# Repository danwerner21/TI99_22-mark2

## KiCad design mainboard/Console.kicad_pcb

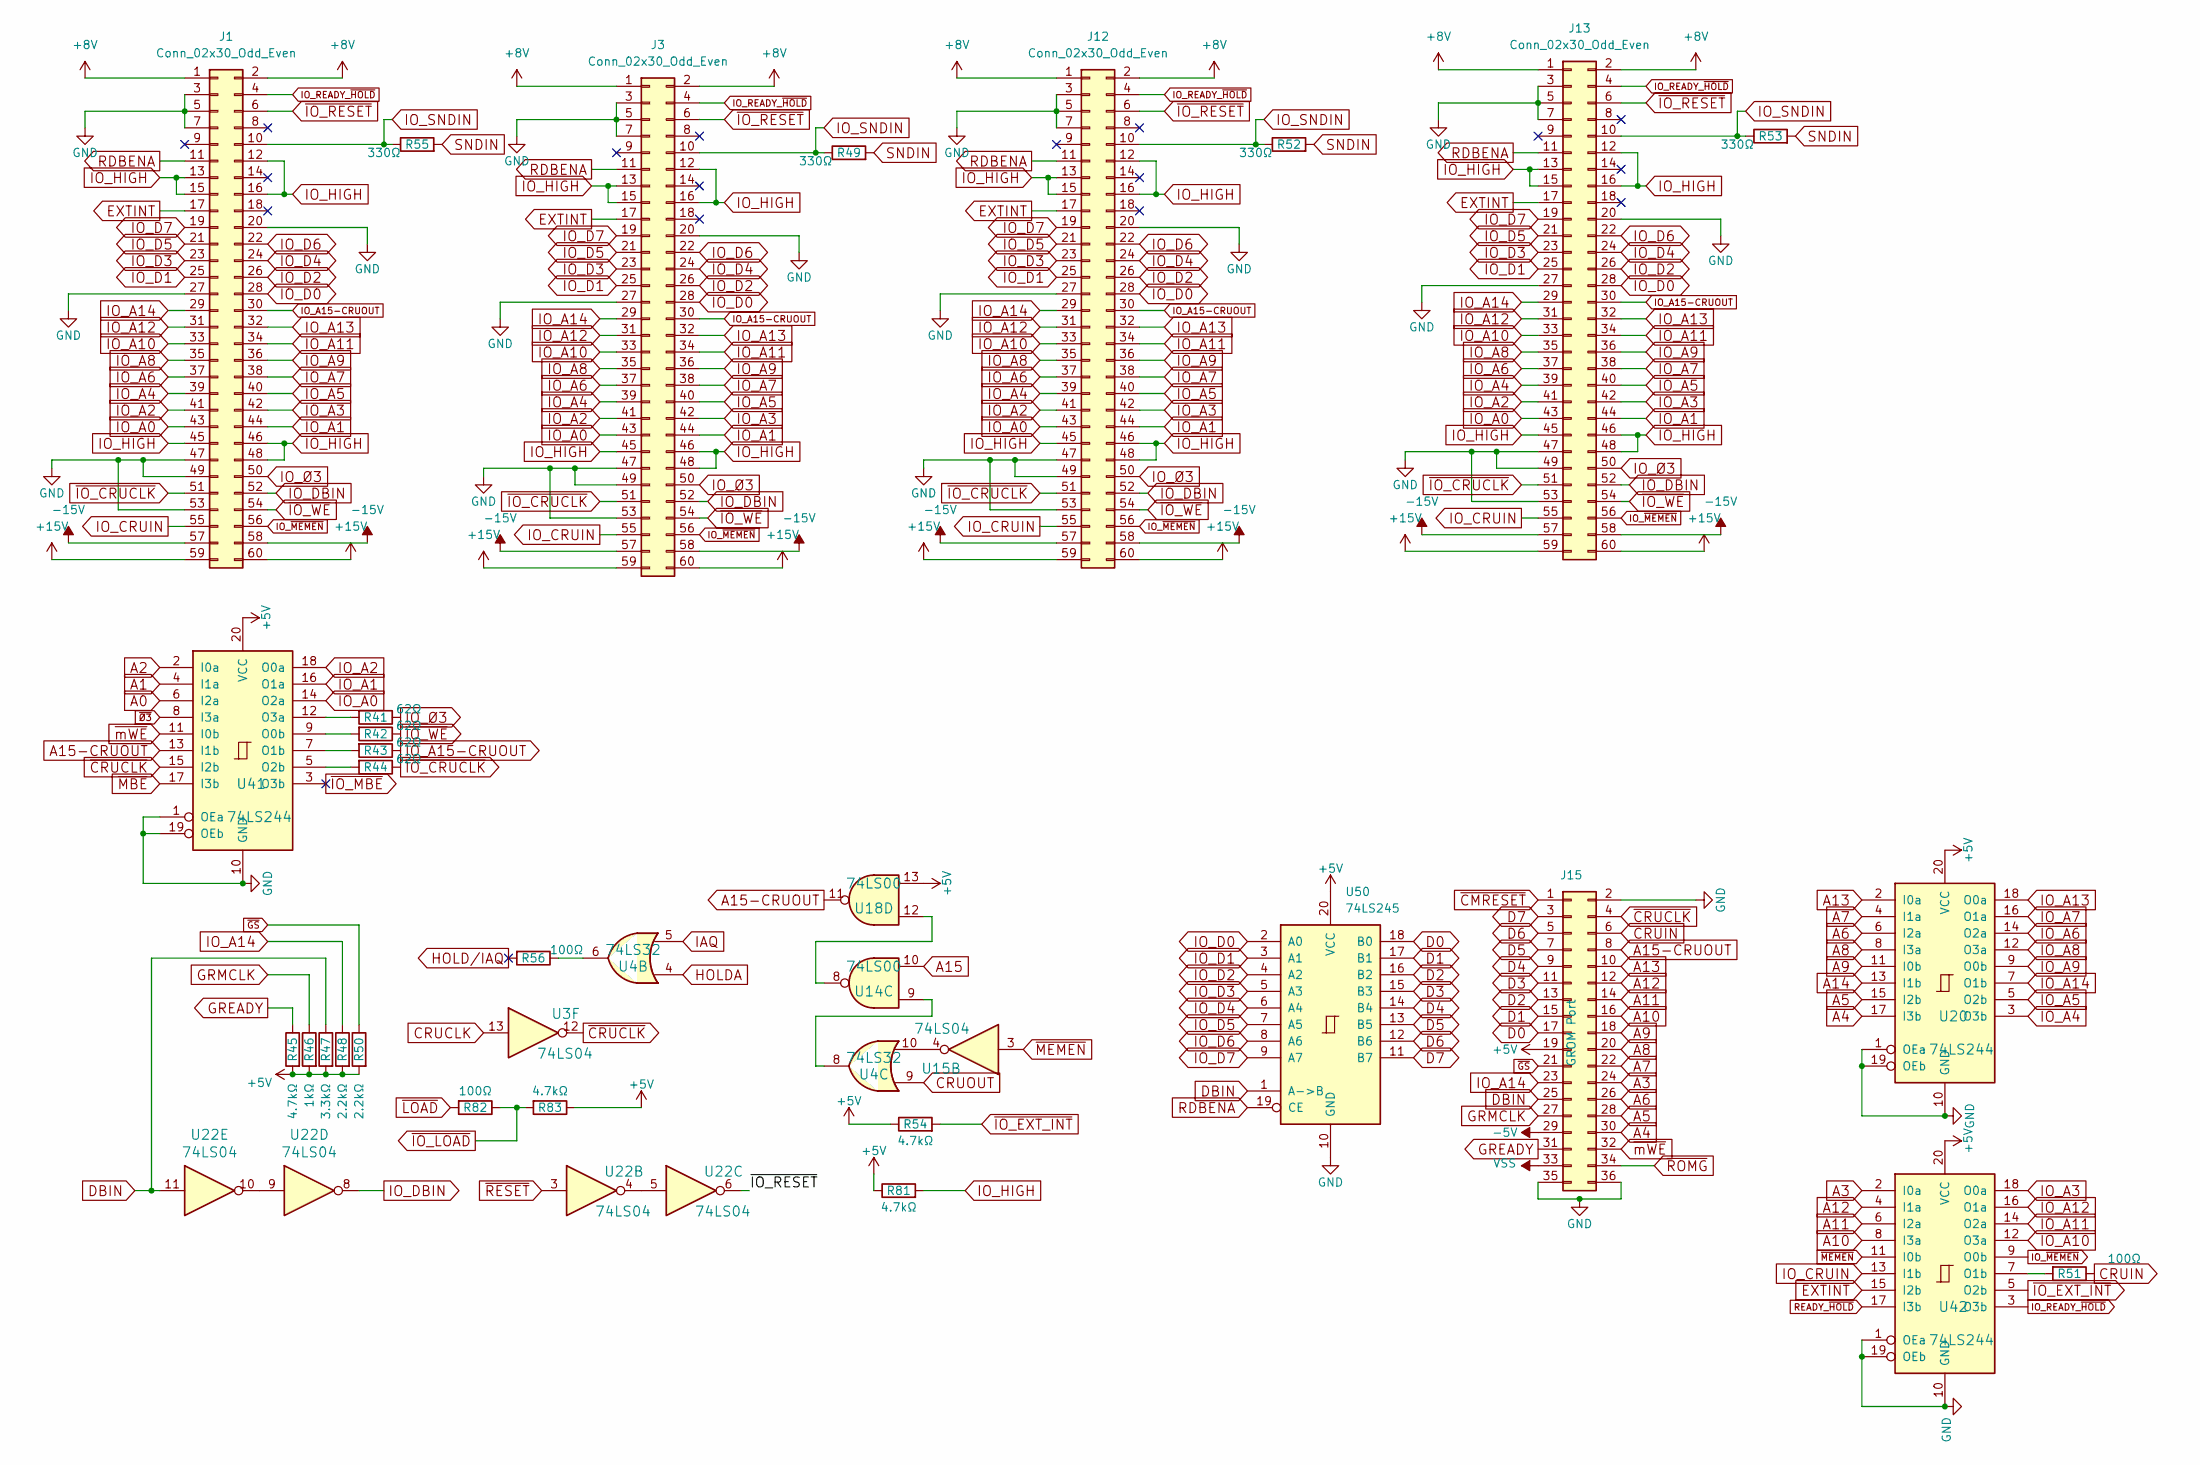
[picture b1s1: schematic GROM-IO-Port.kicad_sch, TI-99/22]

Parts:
J1, J3, J12, J13: Conn_02x30_Odd_Even; STD_DDW_CARDEDGE60
J15: GROM Port; STD_DDW_PINHEAD_V_2x18
R41, R42, R43, R44: 62Ω; STD_DDW_RESISTOR
R45, R54, R81, R83: 4.7kΩ; STD_DDW_RESISTOR
R46: 1kΩ; STD_DDW_RESISTOR
R47: 3.3kΩ; STD_DDW_RESISTOR
R48, R50: 2.2kΩ; STD_DDW_RESISTOR
R49, R52, R53, R55: 330Ω; STD_DDW_RESISTOR
R51, R56, R82: 100Ω; STD_DDW_RESISTOR
U3, U15, U22: 74LS04; STD_DDW_DIP14
U4: 74LS32; STD_DDW_DIP14
U14, U18: 74LS00; STD_DDW_DIP14
U20, U41, U42: 74LS244; STD_DDW_DIP20
U50: 74LS245; STD_DDW_DIP20

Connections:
+5V: J15.19, R45.2, R46.2, R47.2, R48.2, R50.2, R54.1, R81.1, R83.1, U18.13, U20.20 (VCC), U41.20 (VCC), U42.20 (VCC), U50.20 (VCC); also elsewhere on the board
+8V: J1.1, J1.2, J3.1, J3.2, J12.1, J12.2, J13.1, J13.2; also elsewhere on the board
+15V: J1.59, J1.60, J3.59, J3.60, J12.59, J12.60, J13.59, J13.60; also elsewhere on the board
-5V: J15.29; also elsewhere on the board
-15V: J1.57, J1.58, J3.57, J3.58, J12.57, J12.58, J13.57, J13.58; also elsewhere on the board
A0: U41.6 (I2a); also elsewhere on the board
A1: U41.4 (I1a); also elsewhere on the board
A2: U41.2 (I0a); also elsewhere on the board
A3: J15.24, U42.2 (I0a); also elsewhere on the board
A4: J15.30, U20.17 (I3b); also elsewhere on the board
A5: J15.28, U20.15 (I2b); also elsewhere on the board
A6: J15.26, U20.6 (I2a); also elsewhere on the board
A7: J15.22, U20.4 (I1a); also elsewhere on the board
A8: J15.20, U20.8 (I3a); also elsewhere on the board
A9: J15.18, U20.11 (I0b); also elsewhere on the board
A10: J15.16, U42.8 (I3a); also elsewhere on the board
A11: J15.14, U42.6 (I2a); also elsewhere on the board
A12: J15.12, U42.4 (I1a); also elsewhere on the board
A13: J15.10, U20.2 (I0a); also elsewhere on the board
A14: U20.13 (I1b); also elsewhere on the board
A15: U14.10; also elsewhere on the board
A15-CRUOUT: J15.8, U18.11, U41.13 (I1b); also elsewhere on the board
CRUCLK: U3.13; also elsewhere on the board
CRUIN: J15.6, R51.1; also elsewhere on the board
CRUOUT: U4.9; also elsewhere on the board
D0: J15.17, U50.18 (B0); also elsewhere on the board
D1: J15.15, U50.17 (B1); also elsewhere on the board
D2: J15.13, U50.16 (B2); also elsewhere on the board
D3: J15.11, U50.15 (B3); also elsewhere on the board
D4: J15.9, U50.14 (B4); also elsewhere on the board
D5: J15.7, U50.13 (B5); also elsewhere on the board
D6: J15.5, U50.12 (B6); also elsewhere on the board
D7: J15.3, U50.11 (B7); also elsewhere on the board
DBIN: J15.25, R47.1, U22.11, U50.1 (A->B); also elsewhere on the board
EXTINT: J1.17, J3.17, J12.17, J13.17, U42.15 (I2b); also elsewhere on the board
GND: J1.3, J1.5, J1.7, J1.20, J1.27, J1.47, J1.49, J1.53, J3.3, J3.5, J3.7, J3.20, J3.27, J3.47, J3.49, J3.53, J12.3, J12.5, J12.7, J12.20, J12.27, J12.47, J12.49, J12.53, J13.3, J13.5, J13.7, J13.20, J13.27, J13.47, J13.49, J13.53, J15.2, J15.35, J15.36, U20.1 (OEa), U20.10 (GND), U20.19 (OEb), U41.1 (OEa), U41.10 (GND), U41.19 (OEb), U42.1 (OEa), U42.10 (GND), U42.19 (OEb), U50.10 (GND); also elsewhere on the board
GREADY: J15.31, R45.1; also elsewhere on the board
GRMCLK: J15.27, R46.1; also elsewhere on the board
HOLDA: U4.4; also elsewhere on the board
HOLD/IAQ: R56.2
IAQ: U4.5; also elsewhere on the board
IO_A0: J1.43, J3.43, J12.43, J13.43, U41.14 (O2a)
IO_A1: J1.44, J3.44, J12.44, J13.44, U41.16 (O1a)
IO_A2: J1.41, J3.41, J12.41, J13.41, U41.18 (O0a)
IO_A3: J1.42, J3.42, J12.42, J13.42, U42.18 (O0a); also elsewhere on the board
IO_A4: J1.39, J3.39, J12.39, J13.39, U20.3 (O3b); also elsewhere on the board
IO_A5: J1.40, J3.40, J12.40, J13.40, U20.5 (O2b); also elsewhere on the board
IO_A6: J1.37, J3.37, J12.37, J13.37, U20.14 (O2a)
IO_A7: J1.38, J3.38, J12.38, J13.38, U20.16 (O1a)
IO_A8: J1.35, J3.35, J12.35, J13.35, U20.12 (O3a)
IO_A9: J1.36, J3.36, J12.36, J13.36, U20.9 (O0b)
IO_A10: J1.33, J3.33, J12.33, J13.33, U42.12 (O3a)
IO_A11: J1.34, J3.34, J12.34, J13.34, U42.14 (O2a)
IO_A12: J1.31, J3.31, J12.31, J13.31, U42.16 (O1a)
IO_A13: J1.32, J3.32, J12.32, J13.32, U20.18 (O0a)
IO_A14: J1.29, J3.29, J12.29, J13.29, J15.23, R48.1, U20.7 (O1b); also elsewhere on the board
IO_A15-CRUOUT: J1.30, J3.30, J12.30, J13.30, R43.1
IO_CRUIN: J1.55, J3.55, J12.55, J13.55, U42.13 (I1b)
IO_D0: J1.28, J3.28, J12.28, J13.28, U50.2 (A0)
IO_D1: J1.25, J3.25, J12.25, J13.25, U50.3 (A1)
IO_D2: J1.26, J3.26, J12.26, J13.26, U50.4 (A2)
IO_D3: J1.23, J3.23, J12.23, J13.23, U50.5 (A3)
IO_D4: J1.24, J3.24, J12.24, J13.24, U50.6 (A4)
IO_D5: J1.21, J3.21, J12.21, J13.21, U50.7 (A5)
IO_D6: J1.22, J3.22, J12.22, J13.22, U50.8 (A6)
IO_D7: J1.19, J3.19, J12.19, J13.19, U50.9 (A7)
IO_DBIN: J1.52, J3.52, J12.52, J13.52, U22.8
IO_HIGH: J1.12, J1.13, J1.15, J1.16, J1.45, J1.46, J1.48, J3.12, J3.13, J3.15, J3.16, J3.45, J3.46, J3.48, J12.12, J12.13, J12.15, J12.16, J12.45, J12.46, J12.48, J13.12, J13.13, J13.15, J13.16, J13.45, J13.46, J13.48, R81.2
IO_READY_~HOLD: J1.4, J3.4, J12.4, J13.4, U42.3 (O3b)
IO_SNDIN: J1.10, J3.10, J12.10, J13.10, R49.1, R52.1, R53.1, R55.1
IO_~MEMEN: J1.56, J3.56, J12.56, J13.56, U42.9 (O0b)
IO_Ø3: J1.50, J3.50, J12.50, J13.50, R41.1
unnamed: R56.1, U4.6
unnamed: U14.8, U18.12
unnamed: U4.8, U14.9
unnamed: U4.10, U15.4
unnamed: U22.4, U22.5
unnamed: U22.9, U22.10
unnamed: R42.2, U41.9 (O0b)
unnamed: R43.2, U41.7 (O1b)
unnamed: R44.2, U41.5 (O2b)
unnamed: R41.2, U41.12 (O3a)
unnamed: R51.2, U42.7 (O1b)
RDBENA: J1.11, J3.11, J12.11, J13.11, U50.19 (CE)
READY_~HOLD: U42.17 (I3b); also elsewhere on the board
SNDIN: R49.2, R52.2, R53.2, R55.2; also elsewhere on the board
VSS: J15.33; also elsewhere on the board
~CMRESET: J15.1; also elsewhere on the board
~CRUCLK: J15.4, U3.12, U41.15 (I2b)
~GS: J15.21, R50.1; also elsewhere on the board
~IO_CRUCLK: J1.51, J3.51, J12.51, J13.51, R44.1
~IO_EXT_INT: R54.2, U42.5 (O2b)
~IO_LOAD: R82.1, R83.2
~IO_MBE: U41.3 (O3b)
~IO_RESET: J1.6, J3.6, J12.6, J13.6, U22.6
~IO_WE: J1.54, J3.54, J12.54, J13.54, R42.1
~LOAD: R82.2; also elsewhere on the board
~MBE: U41.17 (I3b); also elsewhere on the board
~MEMEN: U15.3, U42.11 (I0b); also elsewhere on the board
~RESET: U22.3; also elsewhere on the board
~ROMG: J15.34; also elsewhere on the board
~mWE: J15.32, U41.11 (I0b); also elsewhere on the board
~Ø3: U41.8 (I3a); also elsewhere on the board

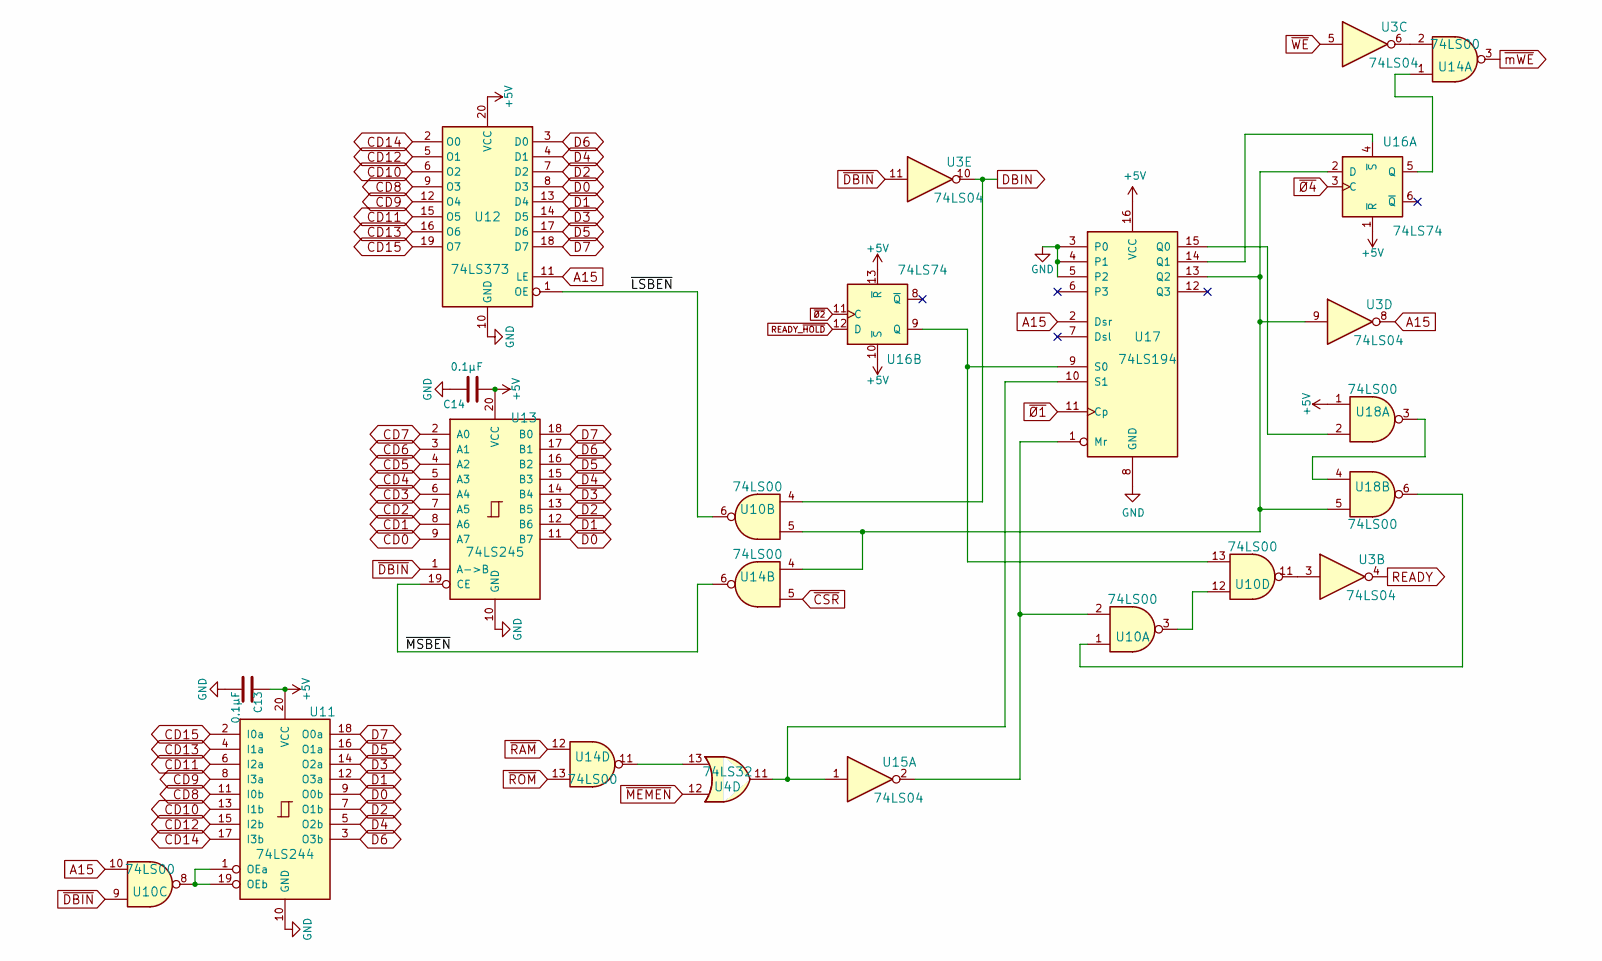
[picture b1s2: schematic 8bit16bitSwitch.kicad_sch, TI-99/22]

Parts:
C13, C14: 0.1µF; STD_DDW_CAP
U3, U15: 74LS04; STD_DDW_DIP14
U4: 74LS32; STD_DDW_DIP14
U10, U14, U18: 74LS00; STD_DDW_DIP14
U11: 74LS244; STD_DDW_DIP20
U12: 74LS373; STD_DDW_DIP20
U13: 74LS245; STD_DDW_DIP20
U16: 74LS74; STD_DDW_DIP14
U17: 74LS194; STD_DDW_DIP16

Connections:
+5V: C13.1, C14.1, U11.20 (VCC), U12.20 (VCC), U13.20 (VCC), U16.1 (~R), U16.10 (~S), U16.13 (~R), U17.16 (VCC), U18.1; also elsewhere on the board
/8Bit16BitSwitch/~LSBEN: U10.6, U12.1 (OE)
/8Bit16BitSwitch/~MSBEN: U13.19 (CE), U14.6
A15: U3.8, U10.10, U12.11 (LE), U17.2 (Dsr); also elsewhere on the board
CD0: U13.9 (A7); also elsewhere on the board
CD1: U13.8 (A6); also elsewhere on the board
CD2: U13.7 (A5); also elsewhere on the board
CD3: U13.6 (A4); also elsewhere on the board
CD4: U13.5 (A3); also elsewhere on the board
CD5: U13.4 (A2); also elsewhere on the board
CD6: U13.3 (A1); also elsewhere on the board
CD7: U13.2 (A0); also elsewhere on the board
CD8: U11.11 (I0b), U12.9 (O3); also elsewhere on the board
CD9: U11.8 (I3a), U12.12 (O4); also elsewhere on the board
CD10: U11.13 (I1b), U12.6 (O2); also elsewhere on the board
CD11: U11.6 (I2a), U12.15 (O5); also elsewhere on the board
CD12: U11.15 (I2b), U12.5 (O1); also elsewhere on the board
CD13: U11.4 (I1a), U12.16 (O6); also elsewhere on the board
CD14: U11.17 (I3b), U12.2 (O0); also elsewhere on the board
CD15: U11.2 (I0a), U12.19 (O7); also elsewhere on the board
D0: U11.9 (O0b), U12.8 (D3), U13.11 (B7); also elsewhere on the board
D1: U11.12 (O3a), U12.13 (D4), U13.12 (B6); also elsewhere on the board
D2: U11.7 (O1b), U12.7 (D2), U13.13 (B5); also elsewhere on the board
D3: U11.14 (O2a), U12.14 (D5), U13.14 (B4); also elsewhere on the board
D4: U11.5 (O2b), U12.4 (D1), U13.15 (B3); also elsewhere on the board
D5: U11.16 (O1a), U12.17 (D6), U13.16 (B2); also elsewhere on the board
D6: U11.3 (O3b), U12.3 (D0), U13.17 (B1); also elsewhere on the board
D7: U11.18 (O0a), U12.18 (D7), U13.18 (B0); also elsewhere on the board
DBIN: U3.10, U10.4; also elsewhere on the board
GND: C13.2, C14.2, U11.10 (GND), U12.10 (GND), U13.10 (GND), U17.3 (P0), U17.4 (P1), U17.5 (P2), U17.8 (GND); also elsewhere on the board
unnamed: U10.1, U18.6
unnamed: U3.3, U10.11
unnamed: U10.3, U10.12
unnamed: U10.8, U11.1 (OEa), U11.19 (OEb)
unnamed: U3.6, U14.2
unnamed: U4.13, U14.11
unnamed: U3.9, U10.5, U14.4, U16.2 (D), U17.13 (Q2), U18.5
unnamed: U14.1, U16.5 (Q)
unnamed: U16.4 (~S), U17.14 (Q1)
unnamed: U10.13, U16.9 (Q), U17.9 (S0)
unnamed: U10.2, U15.2, U17.1 (Mr)
unnamed: U17.15 (Q0), U18.2
unnamed: U4.11, U15.1, U17.10 (S1)
unnamed: U18.3, U18.4
READY: U3.4; also elsewhere on the board
READY_~HOLD: U16.12 (D); also elsewhere on the board
~CSR: U14.5; also elsewhere on the board
~DBIN: U3.11, U10.9, U13.1 (A->B); also elsewhere on the board
~MEMEN: U4.12; also elsewhere on the board
~RAM: U14.12; also elsewhere on the board
~ROM: U14.13; also elsewhere on the board
~WE: U3.5; also elsewhere on the board
~mWE: U14.3; also elsewhere on the board
~Ø1: U17.11 (Cp); also elsewhere on the board
~Ø2: U16.11 (C); also elsewhere on the board
~Ø4: U16.3 (C); also elsewhere on the board

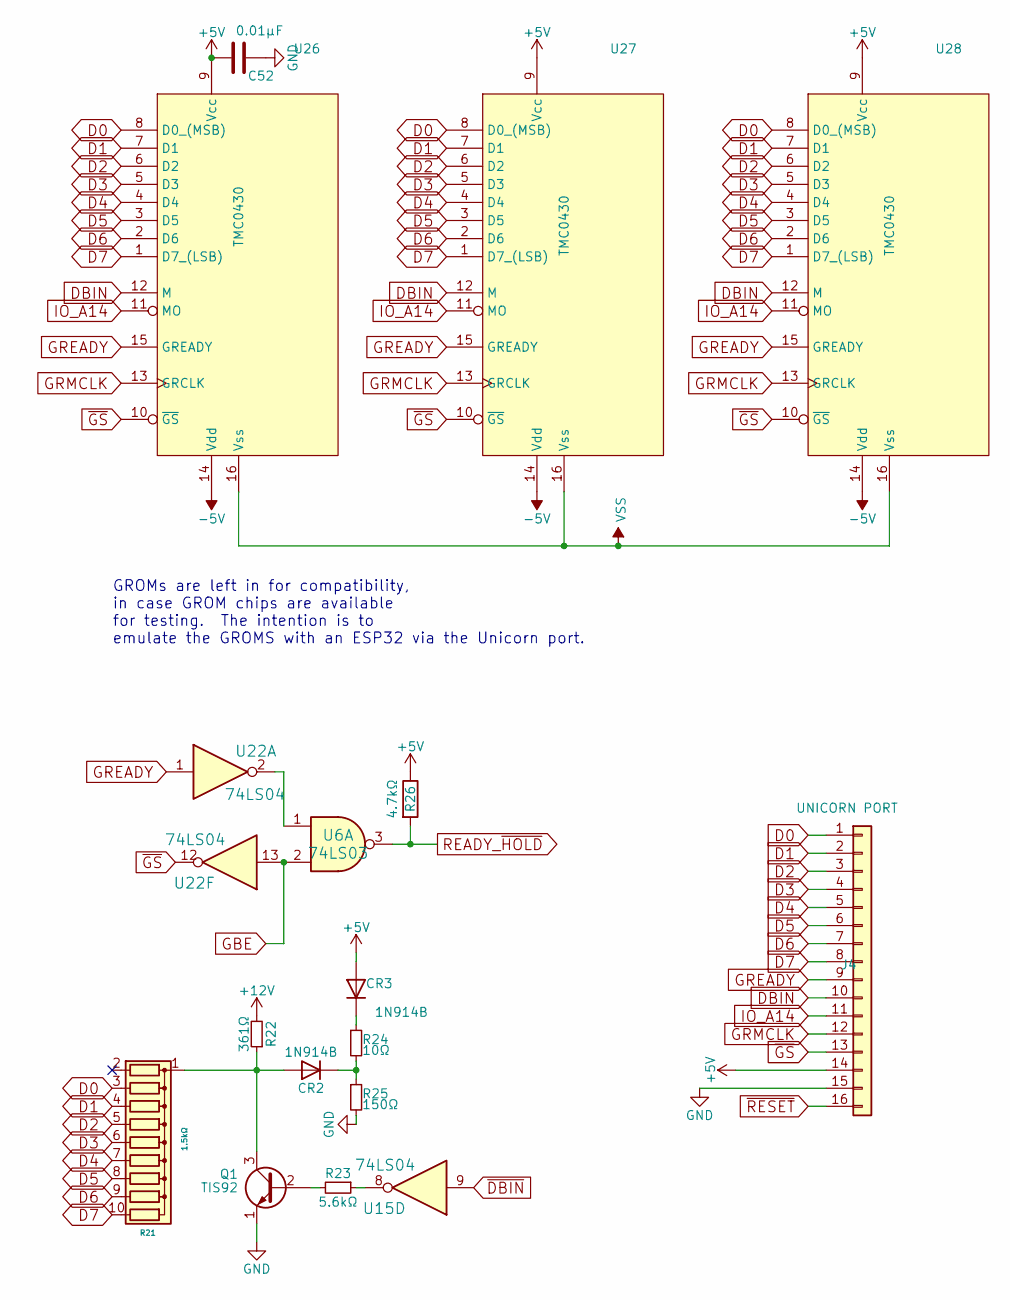
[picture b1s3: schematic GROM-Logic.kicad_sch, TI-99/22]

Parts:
C52: 0.01µF; STD_DDW_CAP
CR2, CR3: 1N914B; STD_DDW_DIODE
J4: UNICORN PORT; STD_DDW_PINHEAD_V_1x16
Q1: TIS92; STD_DDW_TO92
R21: 1.5kΩ; STD_DDW_SIP10
R22: 361Ω; STD_DDW_RESISTOR
R23: 5.6kΩ; STD_DDW_RESISTOR
R24: 10Ω; STD_DDW_RESISTOR
R25: 150Ω; STD_DDW_RESISTOR
R26: 4.7kΩ; STD_DDW_RESISTOR
U6: 74LS03; STD_DDW_DIP14
U15, U22: 74LS04; STD_DDW_DIP14
U26, U27, U28: TMC0430; STD_DDW_DIP16

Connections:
+5V: C52.1, CR3.2 (A), J4.14, R26.1, U26.9 (Vcc), U27.9 (Vcc), U28.9 (Vcc); also elsewhere on the board
+12V: R22.2; also elsewhere on the board
-5V: U26.14 (Vdd), U27.14 (Vdd), U28.14 (Vdd); also elsewhere on the board
D0: J4.1, R21.3 (R2), U26.8 (D0_(MSB)), U27.8 (D0_(MSB)), U28.8 (D0_(MSB)); also elsewhere on the board
D1: J4.2, R21.4 (R3), U26.7 (D1), U27.7 (D1), U28.7 (D1); also elsewhere on the board
D2: J4.3, R21.5 (R4), U26.6 (D2), U27.6 (D2), U28.6 (D2); also elsewhere on the board
D3: J4.4, R21.6 (R5), U26.5 (D3), U27.5 (D3), U28.5 (D3); also elsewhere on the board
D4: J4.5, R21.7 (R6), U26.4 (D4), U27.4 (D4), U28.4 (D4); also elsewhere on the board
D5: J4.6, R21.8 (R7), U26.3 (D5), U27.3 (D5), U28.3 (D5); also elsewhere on the board
D6: J4.7, R21.9 (R8), U26.2 (D6), U27.2 (D6), U28.2 (D6); also elsewhere on the board
D7: J4.8, R21.10 (R9), U26.1 (D7_(LSB)), U27.1 (D7_(LSB)), U28.1 (D7_(LSB)); also elsewhere on the board
DBIN: J4.10, U26.12 (M), U27.12 (M), U28.12 (M); also elsewhere on the board
GBE: U6.2, U22.13; also elsewhere on the board
GND: C52.2, J4.15, Q1.1 (E), R25.2; also elsewhere on the board
GREADY: J4.9, U22.1, U26.15 (GREADY), U27.15 (GREADY), U28.15 (GREADY); also elsewhere on the board
GRMCLK: J4.12, U26.13 (GRCLK), U27.13 (GRCLK), U28.13 (GRCLK); also elsewhere on the board
IO_A14: J4.11, U26.11 (MO), U27.11 (MO), U28.11 (MO); also elsewhere on the board
unnamed: CR2.2 (A), Q1.3 (C), R21.1 (common), R22.1
unnamed: CR2.1 (K), R24.2, R25.1
unnamed: CR3.1 (K), R24.1
unnamed: Q1.2 (B), R23.2
unnamed: R23.1, U15.8
unnamed: U6.1, U22.2
READY_~HOLD: R26.2, U6.3; also elsewhere on the board
VSS: U26.16 (Vss), U27.16 (Vss), U28.16 (Vss); also elsewhere on the board
~DBIN: U15.9; also elsewhere on the board
~GS: J4.13, U22.12, U26.10 (~GS), U27.10 (~GS), U28.10 (~GS); also elsewhere on the board
~RESET: J4.16; also elsewhere on the board

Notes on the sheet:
GROMs are left in for compatibility, in case GROM chips are available for testing. The intention is to emulate the GROMS with an ESP32 via the Unicorn port.

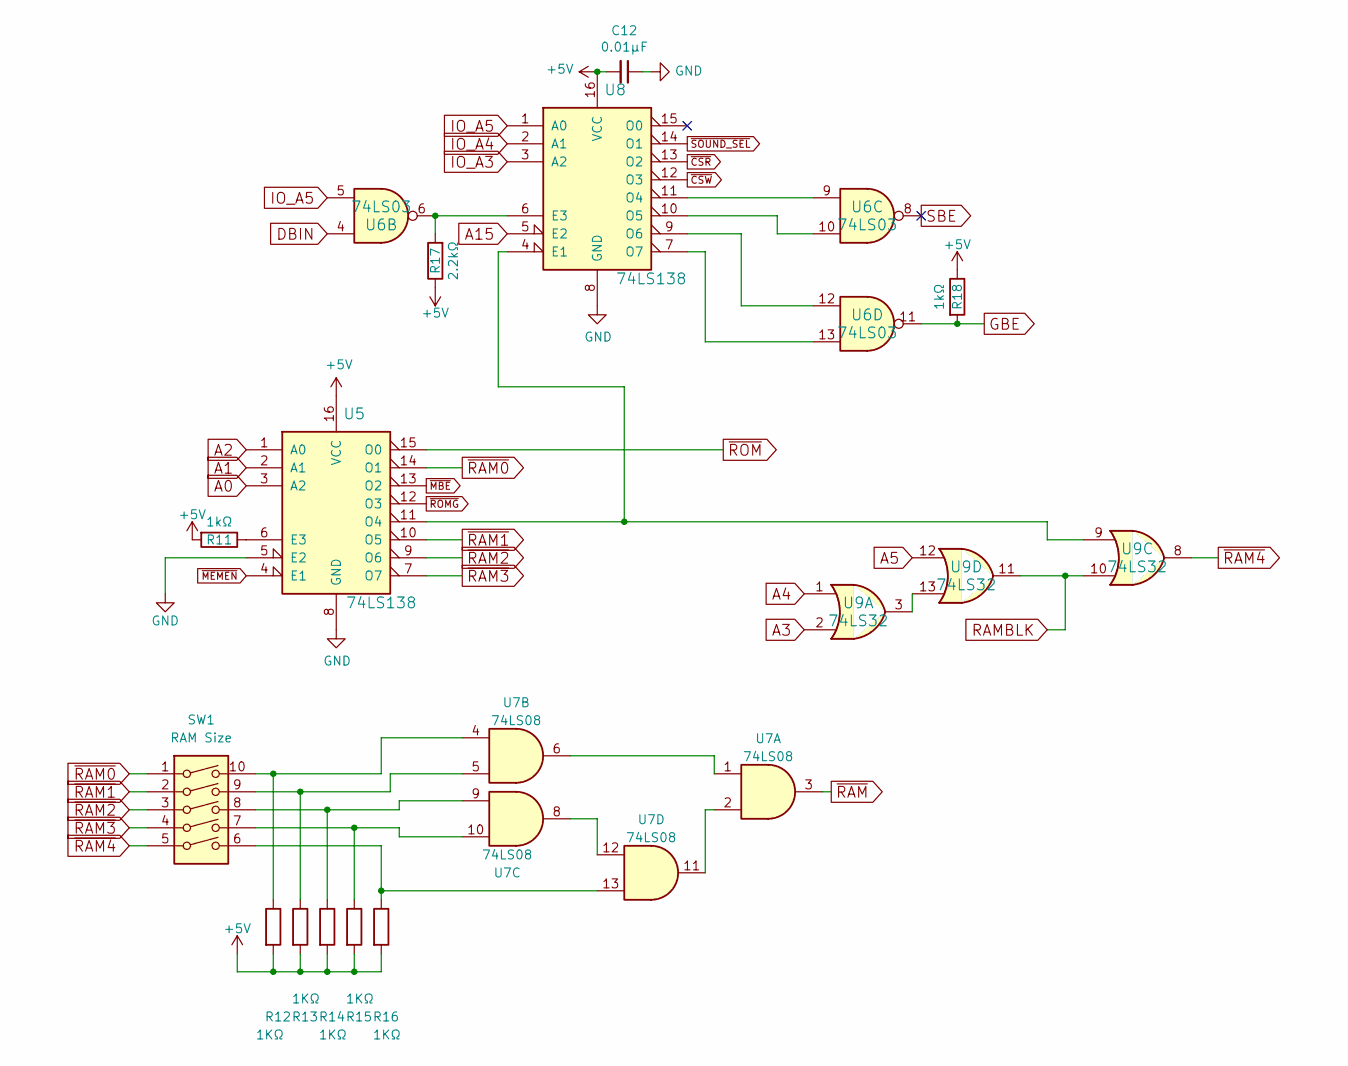
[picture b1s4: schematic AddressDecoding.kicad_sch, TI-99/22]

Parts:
C12: 0.01µF; STD_DDW_CAP
R11, R18: 1kΩ; STD_DDW_RESISTOR
R12, R13, R14, R15, R16: 1KΩ; STD_DDW_RESISTOR
R17: 2.2kΩ; STD_DDW_RESISTOR
SW1: RAM Size; STD_DDW_DIP10
U5, U8: 74LS138; STD_DDW_DIP16
U6: 74LS03; STD_DDW_DIP14
U7: 74LS08; STD_DDW_DIP14
U9: 74LS32; STD_DDW_DIP14

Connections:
+5V: C12.2, R11.2, R12.2, R13.2, R14.2, R15.2, R16.2, R17.1, R18.1, U5.16 (VCC), U8.16 (VCC); also elsewhere on the board
A0: U5.3 (A2); also elsewhere on the board
A1: U5.2 (A1); also elsewhere on the board
A2: U5.1 (A0); also elsewhere on the board
A3: U9.2; also elsewhere on the board
A4: U9.1; also elsewhere on the board
A5: U9.12; also elsewhere on the board
A15: U8.5 (E2); also elsewhere on the board
DBIN: U6.4; also elsewhere on the board
GBE: R18.2, U6.11; also elsewhere on the board
GND: C12.1, U5.5 (E2), U5.8 (GND), U8.8 (GND); also elsewhere on the board
IO_A3: U8.3 (A2); also elsewhere on the board
IO_A4: U8.2 (A1); also elsewhere on the board
IO_A5: U6.5, U8.1 (A0); also elsewhere on the board
unnamed: R12.1, SW1.10, U7.4
unnamed: R13.1, SW1.9, U7.5
unnamed: R14.1, SW1.8, U7.9
unnamed: R15.1, SW1.7, U7.10
unnamed: R16.1, SW1.6, U7.13
unnamed: R11.1, U5.6 (E3)
unnamed: U5.11 (O4), U8.4 (E1), U9.9
unnamed: U7.1, U7.6
unnamed: U7.2, U7.11
unnamed: U7.8, U7.12
unnamed: R17.2, U6.6, U8.6 (E3)
unnamed: U6.9, U8.11 (O4)
unnamed: U6.10, U8.10 (O5)
unnamed: U6.12, U8.9 (O6)
unnamed: U6.13, U8.7 (O7)
unnamed: U9.3, U9.13
RAMBLK: U9.10, U9.11; also elsewhere on the board
SBE: U6.8
~CSR: U8.13 (O2); also elsewhere on the board
~CSW: U8.12 (O3); also elsewhere on the board
~MBE: U5.13 (O2); also elsewhere on the board
~MEMEN: U5.4 (E1); also elsewhere on the board
~RAM0: SW1.1, U5.14 (O1)
~RAM1: SW1.2, U5.10 (O5)
~RAM2: SW1.3, U5.9 (O6)
~RAM3: SW1.4, U5.7 (O7)
~RAM4: SW1.5, U9.8
~RAM: U7.3; also elsewhere on the board
~ROMG: U5.12 (O3); also elsewhere on the board
~ROM: U5.15 (O0); also elsewhere on the board
~SOUND_SEL: U8.14 (O1); also elsewhere on the board

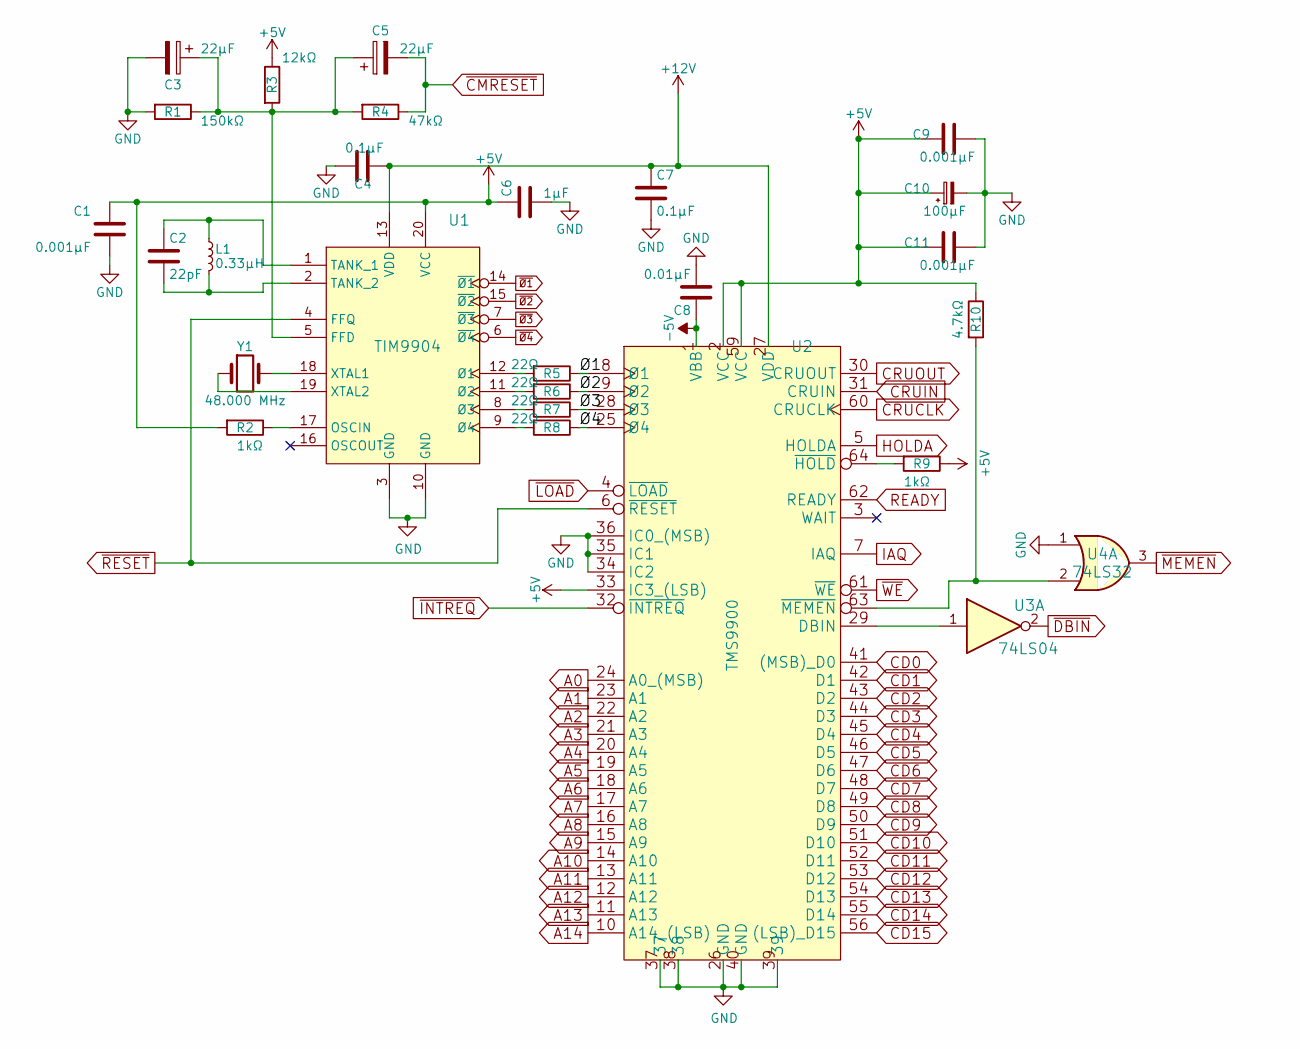
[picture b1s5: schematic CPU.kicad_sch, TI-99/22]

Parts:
C1, C9, C11: 0.001µF; STD_DDW_CAP
C2: 22pF; STD_DDW_CAP
C3, C5: 22µF; STD_DDW_PCAP
C4, C7: 0.1µF; STD_DDW_CAP
C6: 1µF; STD_DDW_CAP
C8: 0.01µF; STD_DDW_CAP
C10: 100µF; STD_DDW_PCAP
L1: 0.33µH; STD_DDW_RESISTOR
R1: 150kΩ; STD_DDW_RESISTOR
R2, R9: 1kΩ; STD_DDW_RESISTOR
R3: 12kΩ; STD_DDW_RESISTOR
R4: 47kΩ; STD_DDW_RESISTOR
R5, R6, R7, R8: 22Ω; STD_DDW_RESISTOR
R10: 4.7kΩ; STD_DDW_RESISTOR
U1: TIM9904; STD_DDW_DIP20
U2: TMS9900; STD_DDW_DIP64_WIDE
U3: 74LS04; STD_DDW_DIP14
U4: 74LS32; STD_DDW_DIP14
Y1: 48.000 MHz; STD_DDW_XTAL

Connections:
+5V: C1.1, C6.1, C9.1, C10.1, C11.1, R2.2, R3.1, R9.1, R10.1, U1.20 (VCC), U2.2 (VCC), U2.33 (IC3_(LSB)), U2.59 (VCC); also elsewhere on the board
+12V: C4.1, C7.1, U1.13 (VDD), U2.27 (VDD); also elsewhere on the board
-5V: C8.1, U2.1 (VBB); also elsewhere on the board
/CPU/Ø1: R5.1, U2.8 (Ø1)
/CPU/Ø2: R6.1, U2.9 (Ø2)
/CPU/Ø3: R7.1, U2.28 (Ø3)
/CPU/Ø4: R8.1, U2.25 (Ø4)
A0: U2.24 (A0_(MSB)); also elsewhere on the board
A1: U2.23 (A1); also elsewhere on the board
A2: U2.22 (A2); also elsewhere on the board
A3: U2.21 (A3); also elsewhere on the board
A4: U2.20 (A4); also elsewhere on the board
A5: U2.19 (A5); also elsewhere on the board
A6: U2.18 (A6); also elsewhere on the board
A7: U2.17 (A7); also elsewhere on the board
A8: U2.16 (A8); also elsewhere on the board
A9: U2.15 (A9); also elsewhere on the board
A10: U2.14 (A10); also elsewhere on the board
A11: U2.13 (A11); also elsewhere on the board
A12: U2.12 (A12); also elsewhere on the board
A13: U2.11 (A13); also elsewhere on the board
A14: U2.10 (A14_(LSB)); also elsewhere on the board
CD0: U2.41 ((MSB)_D0); also elsewhere on the board
CD1: U2.42 (D1); also elsewhere on the board
CD2: U2.43 (D2); also elsewhere on the board
CD3: U2.44 (D3); also elsewhere on the board
CD4: U2.45 (D4); also elsewhere on the board
CD5: U2.46 (D5); also elsewhere on the board
CD6: U2.47 (D6); also elsewhere on the board
CD7: U2.48 (D7); also elsewhere on the board
CD8: U2.49 (D8); also elsewhere on the board
CD9: U2.50 (D9); also elsewhere on the board
CD10: U2.51 (D10); also elsewhere on the board
CD11: U2.52 (D11); also elsewhere on the board
CD12: U2.53 (D12); also elsewhere on the board
CD13: U2.54 (D13); also elsewhere on the board
CD14: U2.55 (D14); also elsewhere on the board
CD15: U2.56 ((LSB)_D15); also elsewhere on the board
CRUCLK: U2.60 (CRUCLK); also elsewhere on the board
CRUIN: U2.31 (CRUIN); also elsewhere on the board
CRUOUT: U2.30 (CRUOUT); also elsewhere on the board
GND: C1.2, C3.2, C4.2, C6.2, C7.2, C8.2, C9.2, C10.2, C11.2, R1.2, U1.3 (GND), U1.10 (GND), U2.26 (GND), U2.34 (IC2), U2.35 (IC1), U2.36 (IC0_(MSB)), U2.37, U2.38, U2.39, U2.40 (GND), U4.1; also elsewhere on the board
HOLDA: U2.5 (HOLDA); also elsewhere on the board
IAQ: U2.7 (IAQ); also elsewhere on the board
unnamed: C3.1, C5.1, R1.1, R3.2, R4.2, U1.5 (FFD)
unnamed: R2.1, U1.17 (OSCIN)
unnamed: C2.1, L1.1, U1.1 (TANK_1)
unnamed: C2.2, L1.2, U1.2 (TANK_2)
unnamed: U1.18 (XTAL1), Y1.2
unnamed: U1.19 (XTAL2), Y1.1
unnamed: R5.2, U1.12 (Ø1)
unnamed: R6.2, U1.11 (Ø2)
unnamed: R7.2, U1.8 (Ø3)
unnamed: R8.2, U1.9 (Ø4)
unnamed: U2.29 (DBIN), U3.1
unnamed: R9.2, U2.64 (~HOLD)
unnamed: R10.2, U2.63 (~MEMEN), U4.2
READY: U2.62 (READY); also elsewhere on the board
~CMRESET: C5.2, R4.1; also elsewhere on the board
~DBIN: U3.2; also elsewhere on the board
~INTREQ: U2.32 (~INTREQ); also elsewhere on the board
~LOAD: U2.4 (~LOAD); also elsewhere on the board
~MEMEN: U4.3; also elsewhere on the board
~RESET: U1.4 (FFQ), U2.6 (~RESET); also elsewhere on the board
~WE: U2.61 (~WE); also elsewhere on the board
~Ø1: U1.14 (~Ø1); also elsewhere on the board
~Ø2: U1.15 (~Ø2); also elsewhere on the board
~Ø3: U1.7 (~Ø3); also elsewhere on the board
~Ø4: U1.6 (~Ø4); also elsewhere on the board
